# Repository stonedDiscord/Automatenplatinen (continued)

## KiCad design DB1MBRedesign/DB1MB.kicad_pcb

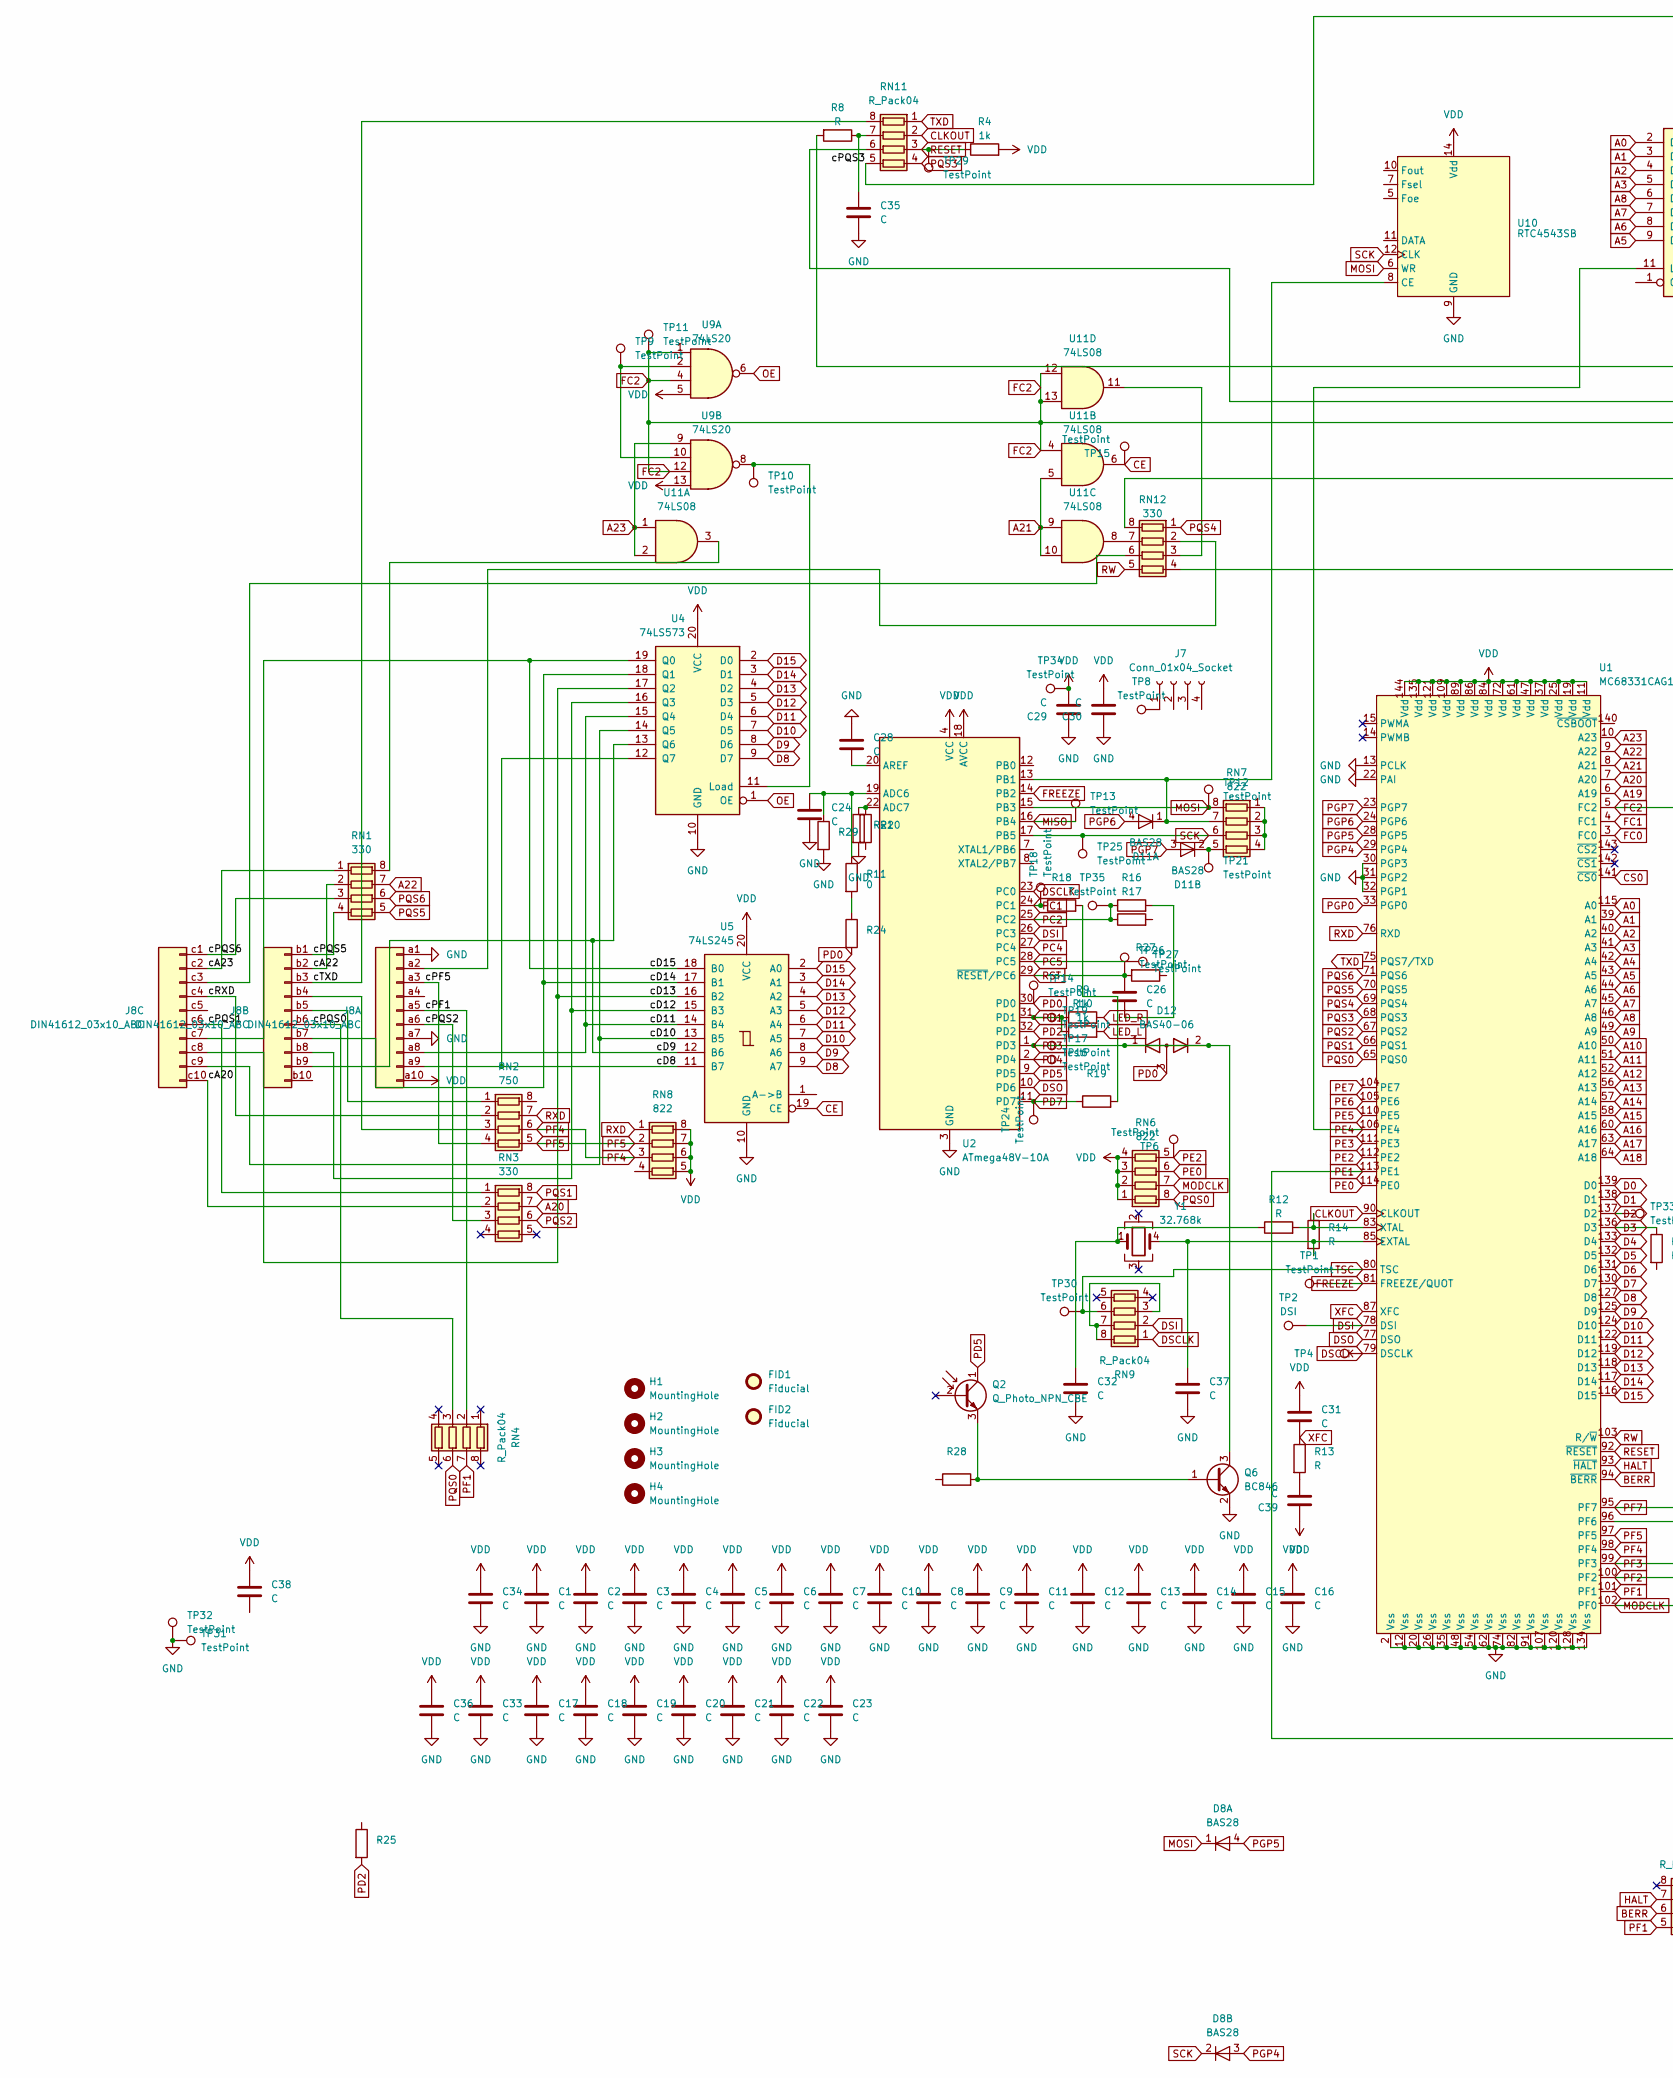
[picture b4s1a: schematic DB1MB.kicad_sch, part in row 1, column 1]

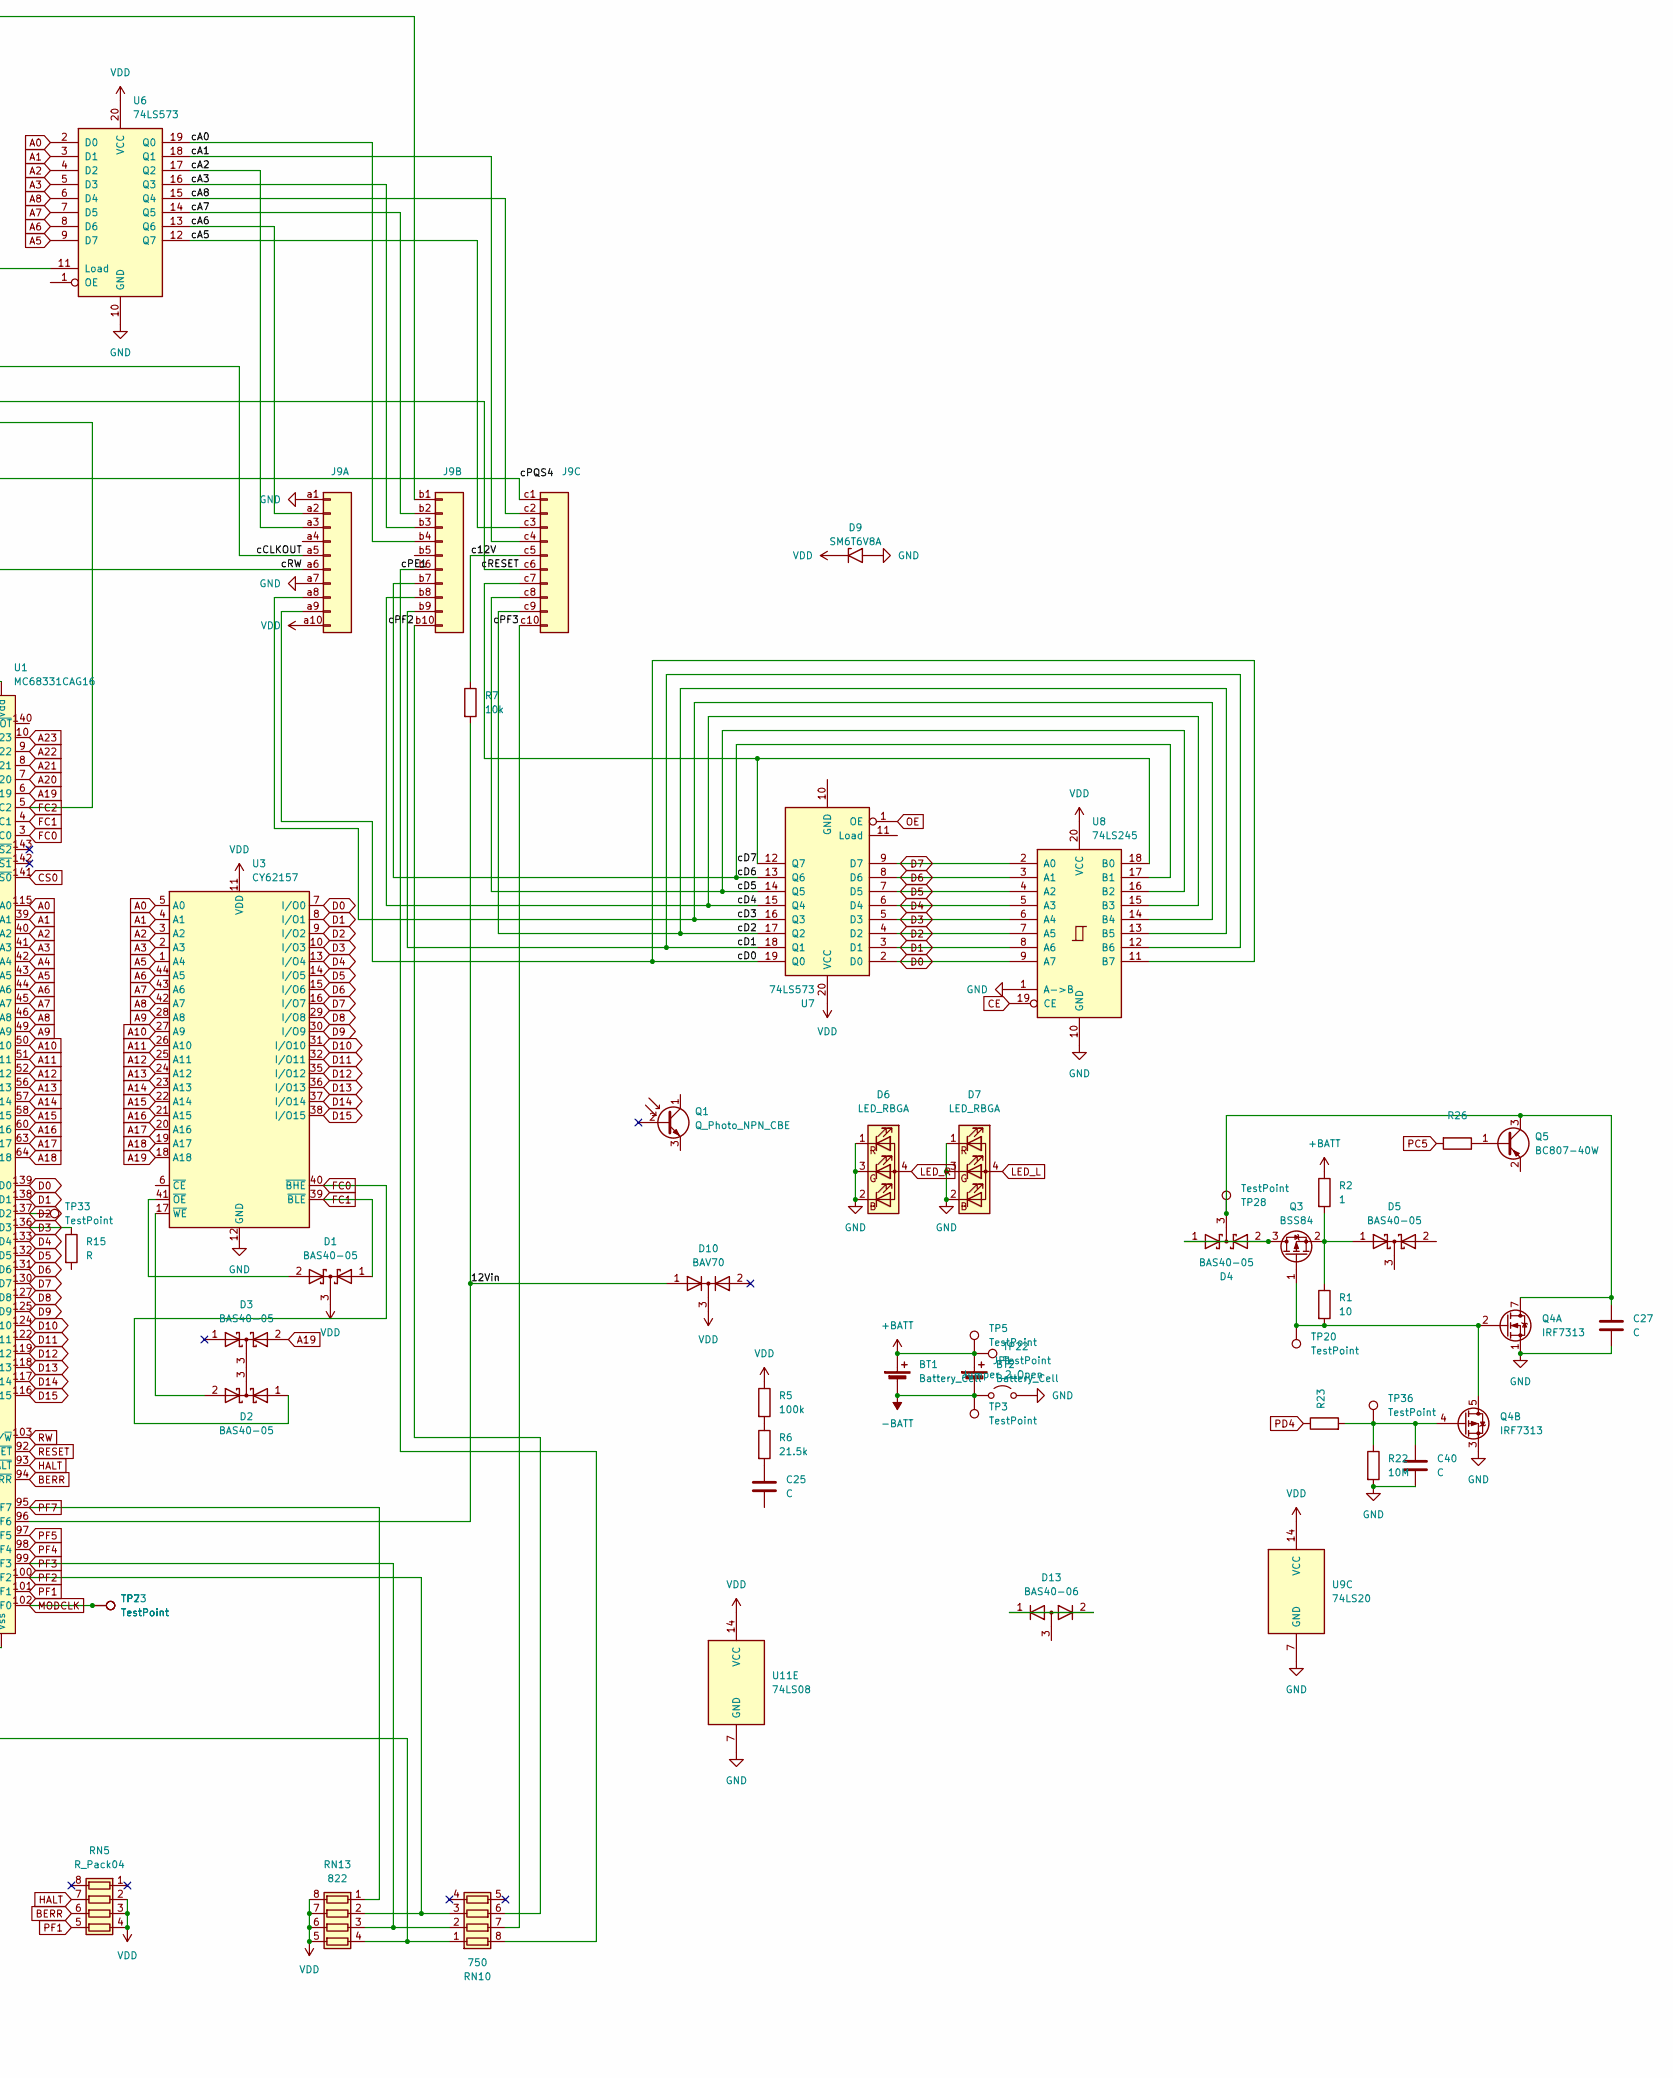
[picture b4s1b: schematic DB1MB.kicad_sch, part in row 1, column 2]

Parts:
BT1, BT2: Battery_Cell; Battery_CR2450
C1, C2, C3, C4, C5, C6, C7, C8, C9, C10, C11, C12, C13, C14, C15, C16, C17, C18, C19, C20, C21, C22, C23, C25, C26, C27, C28, C29, C30, C31, C32, C33, C34, C35, C36, C37, C39: C; C_0805_2012Metric
C24, C38, C40: C; C_1206_3216Metric
D1, D2, D3, D4, D5: BAS40-05; SOT-23-3
D6, D7: LED_RBGA; LED_Cree-PLCC4_3.2x2.8mm_CCW
D8, D11: BAS28; SOT-143
D9: SM6T6V8A; D_SMB
D10: BAV70; TSOT-23
D12, D13: BAS40-06; TSOT-23
FID1, FID2: Fiducial; Fiducial_0.75mm_Mask2.25mm
H1, H2, H3, H4: MountingHole; MountingHole_2.1mm
J7: Conn_01x04_Socket; Deckel
J8, J9: DIN41612_03x10_ABC; DIN41612_R3_3x10_Male_Vertical_THT
JP1: Jumper_2_Open; SolderJumper-2_P1.3mm_Open_Pad1.0x1.5mm
Q1, Q2: Q_Photo_NPN_CBE; Osram_SMD-SmartDIL
Q3: BSS84; SOT-23-3
Q4: IRF7313; SOIC-8_3.9x4.9mm_P1.27mm
Q5: BC807-40W; TSOT-23
Q6: BC846; SOT-23
R1: 10; R_0805_2012Metric
R2: 1; R_0805_2012Metric
R4, R9, R10: 1k; R_0603_1608Metric
R5: 100k; R_0603_1608Metric
R6: 21.5k; R_0603_1608Metric
R7: 10k; R_0603_1608Metric
R8, R12, R13, R15: R; R_0603_1608Metric
R11: 0; R_0603_1608Metric
R14: R; R_1206_3216Metric
R16, R17, R18, R19, R20, R21, R23, R24, R25, R26, R27, R28, R29: R_0603_1608Metric
R22: 10M; R_1206_3216Metric
RN1, RN3, RN12: 330; R_Array_Concave_4x0603
RN2, RN10: 750; R_Array_Concave_4x0603
RN4, RN5, RN9, RN11: R_Pack04; R_Array_Concave_4x0603
RN6, RN7, RN8, RN13: 822; R_Array_Concave_4x0603
TP1, TP6, TP7, TP8, TP9, TP10, TP11, TP12, TP13, TP14, TP15, TP16, TP17, TP18, TP19, TP20, TP21, TP24, TP25, TP26, TP27, TP28, TP29, TP30, TP34, TP35: TestPoint; TestPoint_Pad_D1.0mm
TP2: DSI; TestPoint_Pad_D1.0mm
TP3, TP5, TP32, TP36: TestPoint; TestPoint_Pad_D1.5mm
TP4: DSCLK; TestPoint_Pad_D1.0mm
TP22, TP23, TP31, TP33: TestPoint; TestPoint_Pad_1.0x1.0mm
U1: MC68331CAG16; TQFP-144_20x20mm_P0.5mm
U2: ATmega48V-10A; TQFP-32_7x7mm_P0.8mm
U3: CY62157; TSOP-II-44_10.16x18.41mm_P0.8mm
U4, U6, U7: 74LS573; TSSOP-20_4.4x6.5mm_P0.65mm
U5, U8: 74LS245; TSSOP-20_4.4x6.5mm_P0.65mm
U9: 74LS20; TSSOP-14_4.4x5mm_P0.65mm
U10: RTC4543SB; SOP-18_5.4x11.4mm_P1.27mm
U11: 74LS08; TSSOP-14_4.4x5mm_P0.65mm
Y1: 32.768k; Crystal_SMD_SeikoEpson_MC306-4Pin_8.0x3.2mm

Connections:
+BATT: BT1.1 (+), BT2.1 (+), R2.1, TP5.1 (1_1), TP22.1 (1_1)
-BATT: BT1.2 (-), BT2.2 (-), JP1.1 (A), TP3.1 (1_1)
/12Vin: D10.1 (A), R7.2, U1.96 (PF6)
/c12V: J9.c5, R7.1
/cA0: J9.b4, U6.19 (Q0)
/cA1: J9.c4, U6.18 (Q1)
/cA2: J9.a3, U6.17 (Q2)
/cA3: J9.b3, U6.16 (Q3)
/cA5: J9.c3, U6.12 (Q7)
/cA6: J9.a2, U6.13 (Q6)
/cA7: J9.b2, U6.14 (Q5)
/cA8: J9.c2, U6.15 (Q4)
/cA20: J8.c10, RN3.2 (R2.1)
/cA22: J8.b2, RN1.2 (R2.1)
/cA23: J8.c2, RN1.1 (R1.1)
/cCLKOUT: J9.a5, R8.2
/cD0: J9.a9, U7.19 (Q0), U8.11 (B7)
/cD1: J9.b9, U7.18 (Q1), U8.12 (B6)
/cD2: J9.c9, U7.17 (Q2), U8.13 (B5)
/cD3: J9.a8, U7.16 (Q3), U8.14 (B4)
/cD4: J9.b8, U7.15 (Q4), U8.15 (B3)
/cD5: J9.c8, U7.14 (Q5), U8.16 (B2)
/cD6: J9.b7, U7.13 (Q6), U8.17 (B1)
/cD7: J9.c7, U7.12 (Q7), U8.18 (B0)
/cD8: J8.a9, U4.12 (Q7), U5.11 (B7)
/cD9: J8.b9, U4.13 (Q6), U5.12 (B6)
/cD10: J8.c9, U4.14 (Q5), U5.13 (B5)
/cD11: J8.a8, U4.15 (Q4), U5.14 (B4)
/cD12: J8.b8, U4.16 (Q3), U5.15 (B3)
/cD13: J8.c8, U4.17 (Q2), U5.16 (B2)
/cD14: J8.b7, U4.18 (Q1), U5.17 (B1)
/cD15: J8.c7, U4.19 (Q0), U5.18 (B0)
/cPE1: J9.b6, RN10.8 (R1.2)
/cPF1: J8.a5, RN4.2 (R2.1)
/cPF2: J9.b10, RN10.6 (R3.2)
/cPF3: J9.c10, RN10.7 (R2.2)
/cPF5: J8.a3, RN2.4 (R4.1)
/cPQS0: J8.b6, RN4.3 (R3.1)
/cPQS1: J8.c6, RN3.1 (R1.1)
/cPQS2: J8.a6, RN3.3 (R3.1)
/cPQS3: J9.b1, RN11.5 (R4.2)
/cPQS4: J9.c1, RN12.8 (R1.2)
/cPQS5: J8.b1, RN1.4 (R4.1)
/cPQS6: J8.c1, RN1.3 (R3.1)
/cRESET: J9.c6, RN11.6 (R3.2)
/cRW: J9.a6, RN12.4 (R4.1)
/cRXD: J8.c4, RN2.2 (R2.1)
/cTXD: J8.b3, RN11.8 (R1.2)
A0: U1.115 (A0), U3.5 (A0), U6.2 (D0)
A1: U1.39 (A1), U3.4 (A1), U6.3 (D1)
A2: U1.40 (A2), U3.3 (A2), U6.4 (D2)
A3: U1.41 (A3), U3.2 (A3), U6.5 (D3)
A4: U1.42 (A4)
A5: U1.43 (A5), U3.1 (A4), U6.9 (D7)
A6: U1.44 (A6), U3.44 (A5), U6.8 (D6)
A7: U1.45 (A7), U3.43 (A6), U6.7 (D5)
A8: U1.46 (A8), U3.42 (A7), U6.6 (D4)
A9: U1.49 (A9), U3.28 (A8)
A10: U1.50 (A10), U3.27 (A9)
A11: U1.51 (A11), U3.26 (A10)
A12: U1.52 (A12), U3.25 (A11)
A13: U1.56 (A13), U3.24 (A12)
A14: U1.57 (A14), U3.23 (A13)
A15: U1.58 (A15), U3.22 (A14)
A16: U1.60 (A16), U3.21 (A15)
A17: U1.63 (A17), U3.20 (A16)
A18: U1.64 (A18), U3.19 (A17)
A19: D3.2 (A), U1.6 (A19), U3.18 (A18)
A20: RN3.7 (R2.2), U1.7 (A20)
A21: U1.8 (A21), U11.5, U11.9, U11.10
A22: RN1.7 (R2.2), U1.9 (A22)
A23: U1.10 (A23), U9.9, U11.1, U11.2
BERR: RN5.6 (R3.2), U1.94 (~BERR)
CE: TP15.1 (1_1), U5.19 (CE), U8.19 (CE), U11.6
CLKOUT: RN11.2 (R2.1), U1.90 (CLKOUT)
CS0: U1.141 (~CS0)
D0: U1.139 (D0), U3.7 (I/O0), U7.2 (D0), U8.9 (A7)
D1: U1.138 (D1), U3.8 (I/O1), U7.3 (D1), U8.8 (A6)
D2: TP33.1 (1_1), U1.137 (D2), U3.9 (I/O2), U7.4 (D2), U8.7 (A5)
D3: R15.1, U1.136 (D3), U3.10 (I/O3), U7.5 (D3), U8.6 (A4)
D4: U1.133 (D4), U3.13 (I/O4), U7.6 (D4), U8.5 (A3)
D5: U1.132 (D5), U3.14 (I/O5), U7.7 (D5), U8.4 (A2)
D6: U1.131 (D6), U3.15 (I/O6), U7.8 (D6), U8.3 (A1)
D7: U1.130 (D7), U3.16 (I/O7), U7.9 (D7), U8.2 (A0)
D8: U1.127 (D8), U3.29 (I/O8), U4.9 (D7), U5.9 (A7)
D9: U1.125 (D9), U3.30 (I/O9), U4.8 (D6), U5.8 (A6)
D10: U1.124 (D10), U3.31 (I/O10), U4.7 (D5), U5.7 (A5)
D11: U1.122 (D11), U3.32 (I/O11), U4.6 (D4), U5.6 (A4)
D12: U1.119 (D12), U3.35 (I/O12), U4.5 (D3), U5.5 (A3)
D13: U1.118 (D13), U3.36 (I/O13), U4.4 (D2), U5.4 (A2)
D14: U1.117 (D14), U3.37 (I/O14), U4.3 (D1), U5.3 (A1)
D15: U1.116 (D15), U3.38 (I/O15), U4.2 (D0), U5.2 (A0)
DSCLK: RN9.1 (R1.1), TP4.1 (1_1), U1.79 (DSCLK), U2.23 (PC0)
DSI: RN9.2 (R2.1), TP2.1 (1_1), U1.78 (DSI), U2.26 (PC3)
DSO: U1.77 (DSO), U2.10 (PD6)
FC0: D2.1 (A), U1.3 (FC0), U3.40 (~BHE)
FC1: D1.1 (A), U1.4 (FC1), U3.39 (~BLE)
FC2: TP11.1 (1_1), U1.5 (FC2), U9.1, U9.4, U9.12, U11.4, U11.12, U11.13
FREEZE: TP1.1 (1_1), U1.81 (FREEZE/QUOT), U2.14 (PB2)
GND: C1.2, C2.2, C3.2, C4.2, C5.2, C6.2, C7.2, C8.2, C9.2, C10.2, C11.2, C12.2, C13.2, C14.2, C15.2, C16.2, C17.2, C18.2, C19.2, C20.2, C21.2, C22.2, C23.2, C24.2, C27.2, C28.1, C29.1, C30.1, C32.2, C33.2, C34.2, C35.2, C36.2, C37.2, C40.2, D6.1 (RK), D6.2 (BK), D6.3 (GK), D7.1 (RK), D7.2 (BK), D7.3 (GK), D9.2 (A2), J8.a1, J8.a7, J9.a1, J9.a7, JP1.2 (B), Q4.1 (S), Q4.3 (1), Q6.2 (E), R21.2, R22.2, R29.2, TP31.1 (1_1), TP32.1 (1_1), U1.2 (Vss), U1.12 (Vss), U1.13 (PCLK), U1.20 (Vss), U1.22 (PAI), U1.26 (Vss), U1.30 (PGP3), U1.31 (PGP2), U1.32 (PGP1), U1.35 (Vss), U1.48 (Vss), U1.54 (Vss), U1.62 (Vss), U1.74 (Vss), U1.82 (Vss), U1.91 (Vss), U1.107 (Vss), U1.120 (Vss), U1.128 (Vss), U1.134 (Vss), U2.3 (GND), U2.5 (GND), U2.21 (GND), U3.12 (GND), U3.34 (GND), U4.10 (GND), U5.10 (GND), U6.10 (GND), U8.1 (A->B), U8.10 (GND), U9.7 (GND), U10.9 (GND), U11.7 (GND)
HALT: RN5.7 (R2.2), U1.93 (~HALT)
LED_L: D7.4 (A), R10.2
LED_R: D6.4 (A), R9.2
MISO: TP13.1 (1_1), U2.16 (PB4)
MODCLK: RN6.7 (R2.2), TP7.1 (1_1), TP23.1 (1_1), U1.102 (PF0)
MOSI: D8.1 (K), RN7.8 (R1.2), TP12.1 (1_1), U2.15 (PB3), U10.6 (WR)
unnamed: C25.1, R6.2
unnamed: C26.2, R16.2
unnamed: C32.1, R12.1, Y1.1
unnamed: C39.2, R13.2
unnamed: D2.3 (K), D3.3 (K)
unnamed: C27.1, D4.3 (K), Q4.7 (D), Q4.8 (D), Q5.3 (C), TP28.1 (1_1)
unnamed: D11.1 (K), RN7.7 (R2.2), U2.13 (PB1), U10.8 (CE)
unnamed: D11.2 (K), RN7.5 (R4.2), TP21.1 (1_1)
unnamed: D13.1 (K), D13.2 (K)
unnamed: J7.1 (Pin_1_1), TP8.1 (1_1)
unnamed: J8.a2, RN12.2 (R2.1)
unnamed: J8.b4, RN2.3 (R3.1)
unnamed: J8.b5, RN2.1 (R1.1)
unnamed: J8.c3, RN12.6 (R3.2)
unnamed: Q2.3 (E), Q6.1 (B), R28.2
unnamed: D4.1 (A), D4.2 (A), Q3.3 (D)
unnamed: Q3.1 (G), Q4.2 (G), Q4.5 (D), Q4.6 (D), R1.2, TP20.1 (1_1)
unnamed: D5.1 (A_1), Q3.2 (S), R1.1, R2.2
unnamed: C40.1, Q4.4 (G), R22.1, R23.2, TP36.1 (1_1)
unnamed: Q5.1 (B), R26.1
unnamed: R5.2, R6.1
unnamed: R11.2, R24.1
unnamed: R18.2, R19.2
unnamed: RN1.8 (R1.2), U11.3
unnamed: RN7.1 (R1.1), RN7.2 (R2.1), RN7.3 (R3.1), RN7.4 (R4.1)
unnamed: RN9.3 (R3.1), RN9.7 (R2.2), RN9.8 (R1.2)
unnamed: C35.1, R8.1, RN11.7 (R2.2)
unnamed: RN12.7 (R2.2), U11.8
unnamed: RN12.3 (R3.1), U11.11
unnamed: TP9.1 (1_1), U9.2, U9.10
unnamed: C37.1, R14.2, U1.85 (EXTAL), Y1.4
unnamed: R12.2, R14.1, U1.83 (XTAL)
unnamed: C24.1, R11.1, R29.1, U2.19 (ADC6)
unnamed: R20.1, R21.1, U2.22 (ADC7)
unnamed: C28.2, U2.20 (AREF)
unnamed: D1.2 (A), U3.41 (~OE)
unnamed: D2.2 (A), U3.17 (~WE)
unnamed: TP10.1 (1_1), U4.11 (Load), U9.8
OE: U4.1 (OE), U7.1 (OE), U9.6
PC1: R18.1, TP18.1 (1_1), U2.24 (PC1)
PC2: R16.1, R17.1, TP35.1 (1_1), U2.25 (PC2)
PC4: U2.27 (PC4)
PC5: R26.2, TP27.1 (1_1), U2.28 (PC5)
PD0: D12.3 (A), R24.2, TP14.1 (1_1), U2.30 (PD0)
PD1: R9.1, R10.1, TP19.1 (1_1), U2.31 (PD1)
PD2: R25.2, U2.32 (PD2)
PD3: D12.1 (K), D12.2 (K), Q6.3 (C), TP17.1 (1_1), U2.1 (PD3)
PD4: R23.1, TP16.1 (1_1), U2.2 (PD4)
PD5: Q2.1 (C), U2.9 (PD5)
PD7: R19.1, TP24.1 (1_1), U2.11 (PD7)
PE0: RN6.6 (R3.2), U1.114 (PE0)
PE1: RN10.1 (R1.1), RN13.4 (R4.1), U1.113 (PE1)
PE2: RN6.5 (R4.2), TP6.1 (1_1), U1.112 (PE2)
PE3: U1.111 (PE3)
PE4: U1.106 (PE4), U6.11 (Load)
PE5: U1.110 (PE5)
PE6: U1.105 (PE6)
PE7: U1.104 (PE7)
PF1: RN4.7 (R2.2), RN5.5 (R4.2), U1.101 (PF1)
PF2: RN10.3 (R3.1), RN13.2 (R2.1), U1.100 (PF2)
PF3: RN10.2 (R2.1), RN13.3 (R3.1), U1.99 (PF3)
PF4: RN2.6 (R3.2), RN8.3 (R3.1), U1.98 (PF4)
PF5: RN2.5 (R4.2), RN8.2 (R2.1), U1.97 (PF5)
PF7: RN13.1 (R1.1), U1.95 (PF7)
PGP0: U1.33 (PGP0)
PGP4: D8.3 (A), U1.29 (PGP4)
PGP5: D8.4 (A), U1.28 (PGP5)
PGP6: D11.4 (A), U1.24 (PGP6)
PGP7: D11.3 (A), U1.23 (PGP7)
PQS0: RN4.6 (R3.2), RN6.8 (R1.2), U1.65 (PQS0)
PQS1: RN3.8 (R1.2), U1.66 (PQS1)
PQS2: RN3.6 (R3.2), U1.67 (PQS2)
PQS3: RN11.4 (R4.1), U1.68 (PQS3)
PQS4: RN12.1 (R1.1), U1.69 (PQS4)
PQS5: RN1.5 (R4.2), U1.70 (PQS5)
PQS6: RN1.6 (R3.2), U1.71 (PQS6)
RESET: R4.1, RN11.3 (R3.1), TP29.1 (1_1), U1.92 (~RESET)
RST: C26.1, R27.2, TP26.1 (1_1), U2.29 (~RESET/PC6)
RW: RN12.5 (R4.2), U1.103 (R/~W)
RXD: RN2.7 (R2.2), RN8.1 (R1.1), U1.76 (RXD)
SCK: D8.2 (K), RN7.6 (R3.2), TP25.1 (1_1), U2.17 (PB5), U10.12 (CLK)
TSC: RN9.6 (R3.2), TP30.1 (1_1), U1.80 (TSC)
TXD: RN11.1 (R1.1), U1.75 (PQS7/TXD)
VDD: C1.1, C2.1, C3.1, C4.1, C5.1, C6.1, C7.1, C8.1, C9.1, C10.1, C11.1, C12.1, C13.1, C14.1, C15.1, C16.1, C17.1, C18.1, C19.1, C20.1, C21.1, C22.1, C23.1, C29.2, C30.2, C31.1, C33.1, C34.1, C36.1, C38.1, C39.1, D1.3 (K), D9.1 (A1), D10.3 (K), J8.a10, J9.a10, R4.2, R5.1, RN5.2 (R2.1), RN5.3 (R3.1), RN5.4 (R4.1), RN6.1 (R1.1), RN6.2 (R2.1), RN6.3 (R3.1), RN6.4 (R4.1), RN8.5 (R4.2), RN8.6 (R3.2), RN8.7 (R2.2), RN8.8 (R1.2), RN13.5 (R4.2), RN13.6 (R3.2), RN13.7 (R2.2), RN13.8 (R1.2), TP34.1 (1_1), U1.11 (Vdd), U1.19 (Vdd), U1.25 (Vdd), U1.37 (Vdd), U1.47 (Vdd), U1.61 (Vdd), U1.72 (Vdd), U1.84 (Vdd), U1.86 (Vdd), U1.89 (Vdd), U1.109 (Vdd), U1.121 (Vdd), U1.135 (Vdd), U1.144 (Vdd), U2.4 (VCC), U2.6 (VCC), U2.18 (AVCC), U3.11 (VDD), U3.33 (VDD), U4.20 (VCC), U5.20 (VCC), U6.20 (VCC), U7.20 (VCC), U8.20 (VCC), U9.5, U9.13, U9.14 (VCC), U10.14 (Vdd), U11.14 (VCC)
XFC: C31.2, R13.1, U1.87 (XFC)

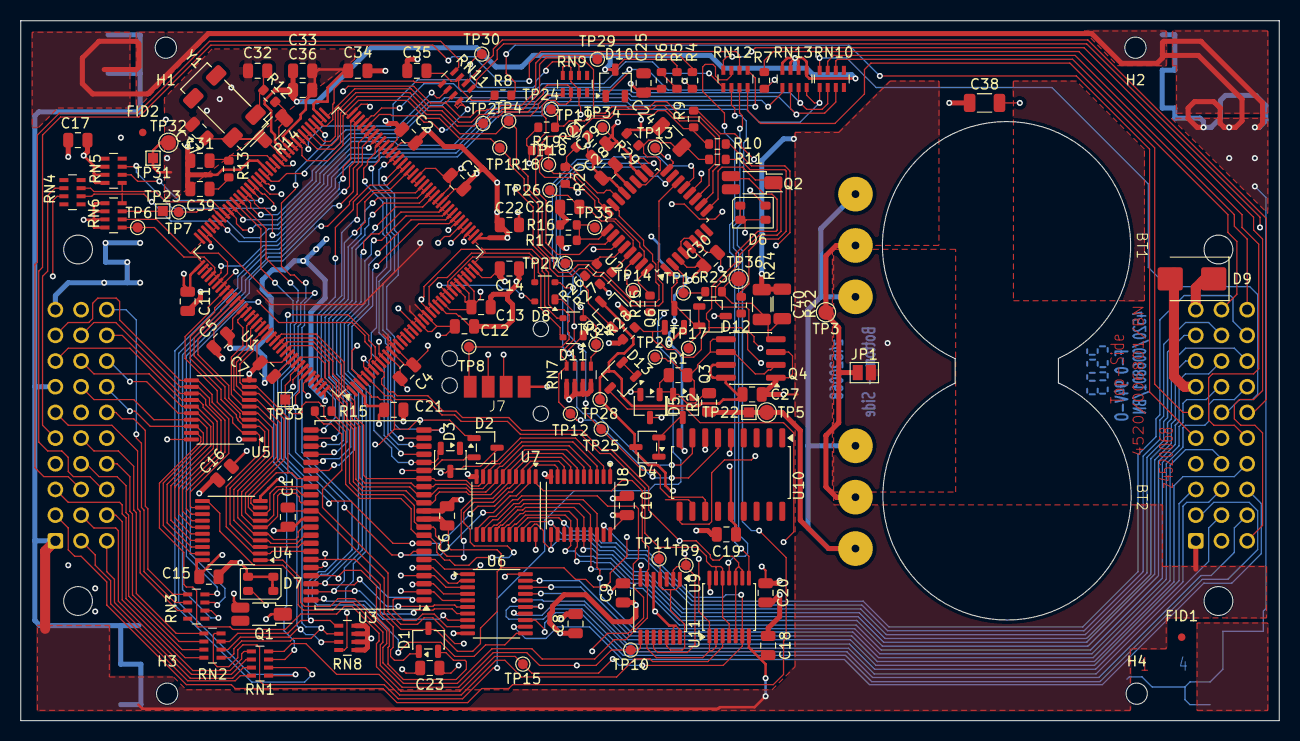
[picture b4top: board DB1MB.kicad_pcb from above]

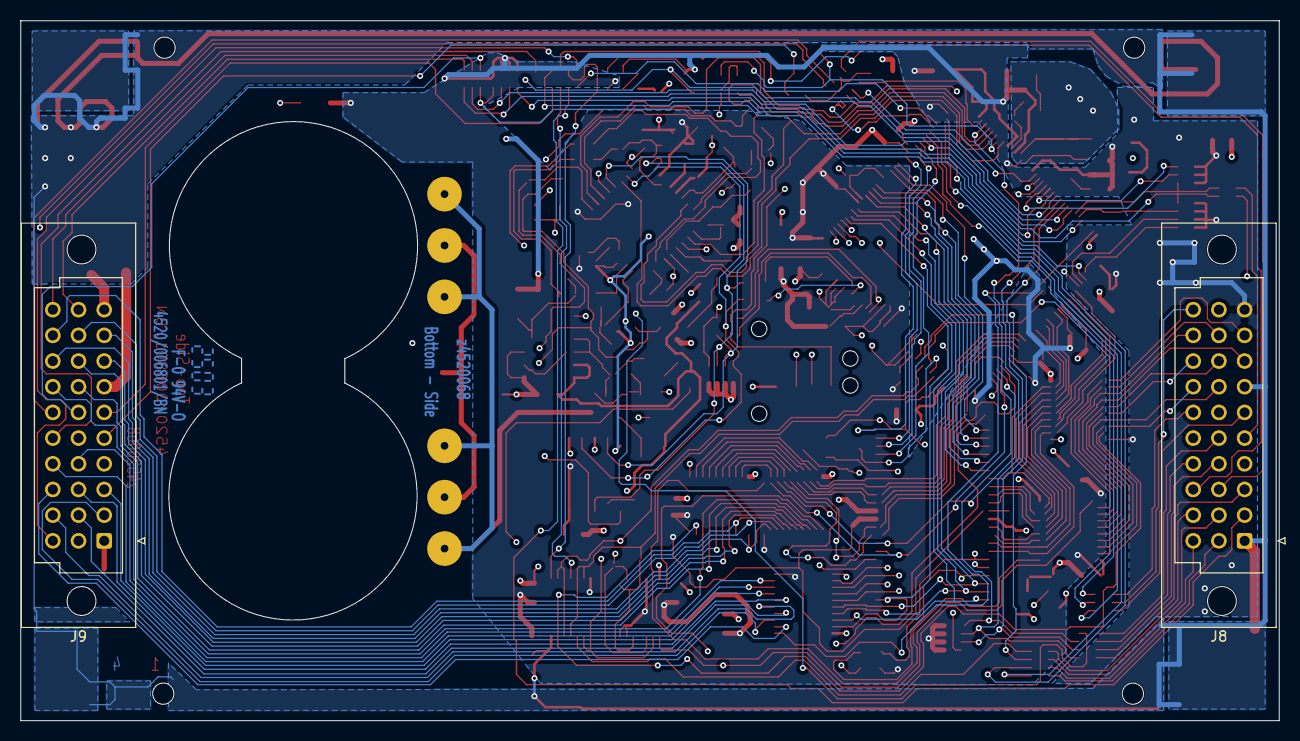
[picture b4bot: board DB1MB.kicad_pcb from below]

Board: 4 copper layers, 124.5 x 69.2 mm, 160 parts (2 on the bottom side), 183 nets.

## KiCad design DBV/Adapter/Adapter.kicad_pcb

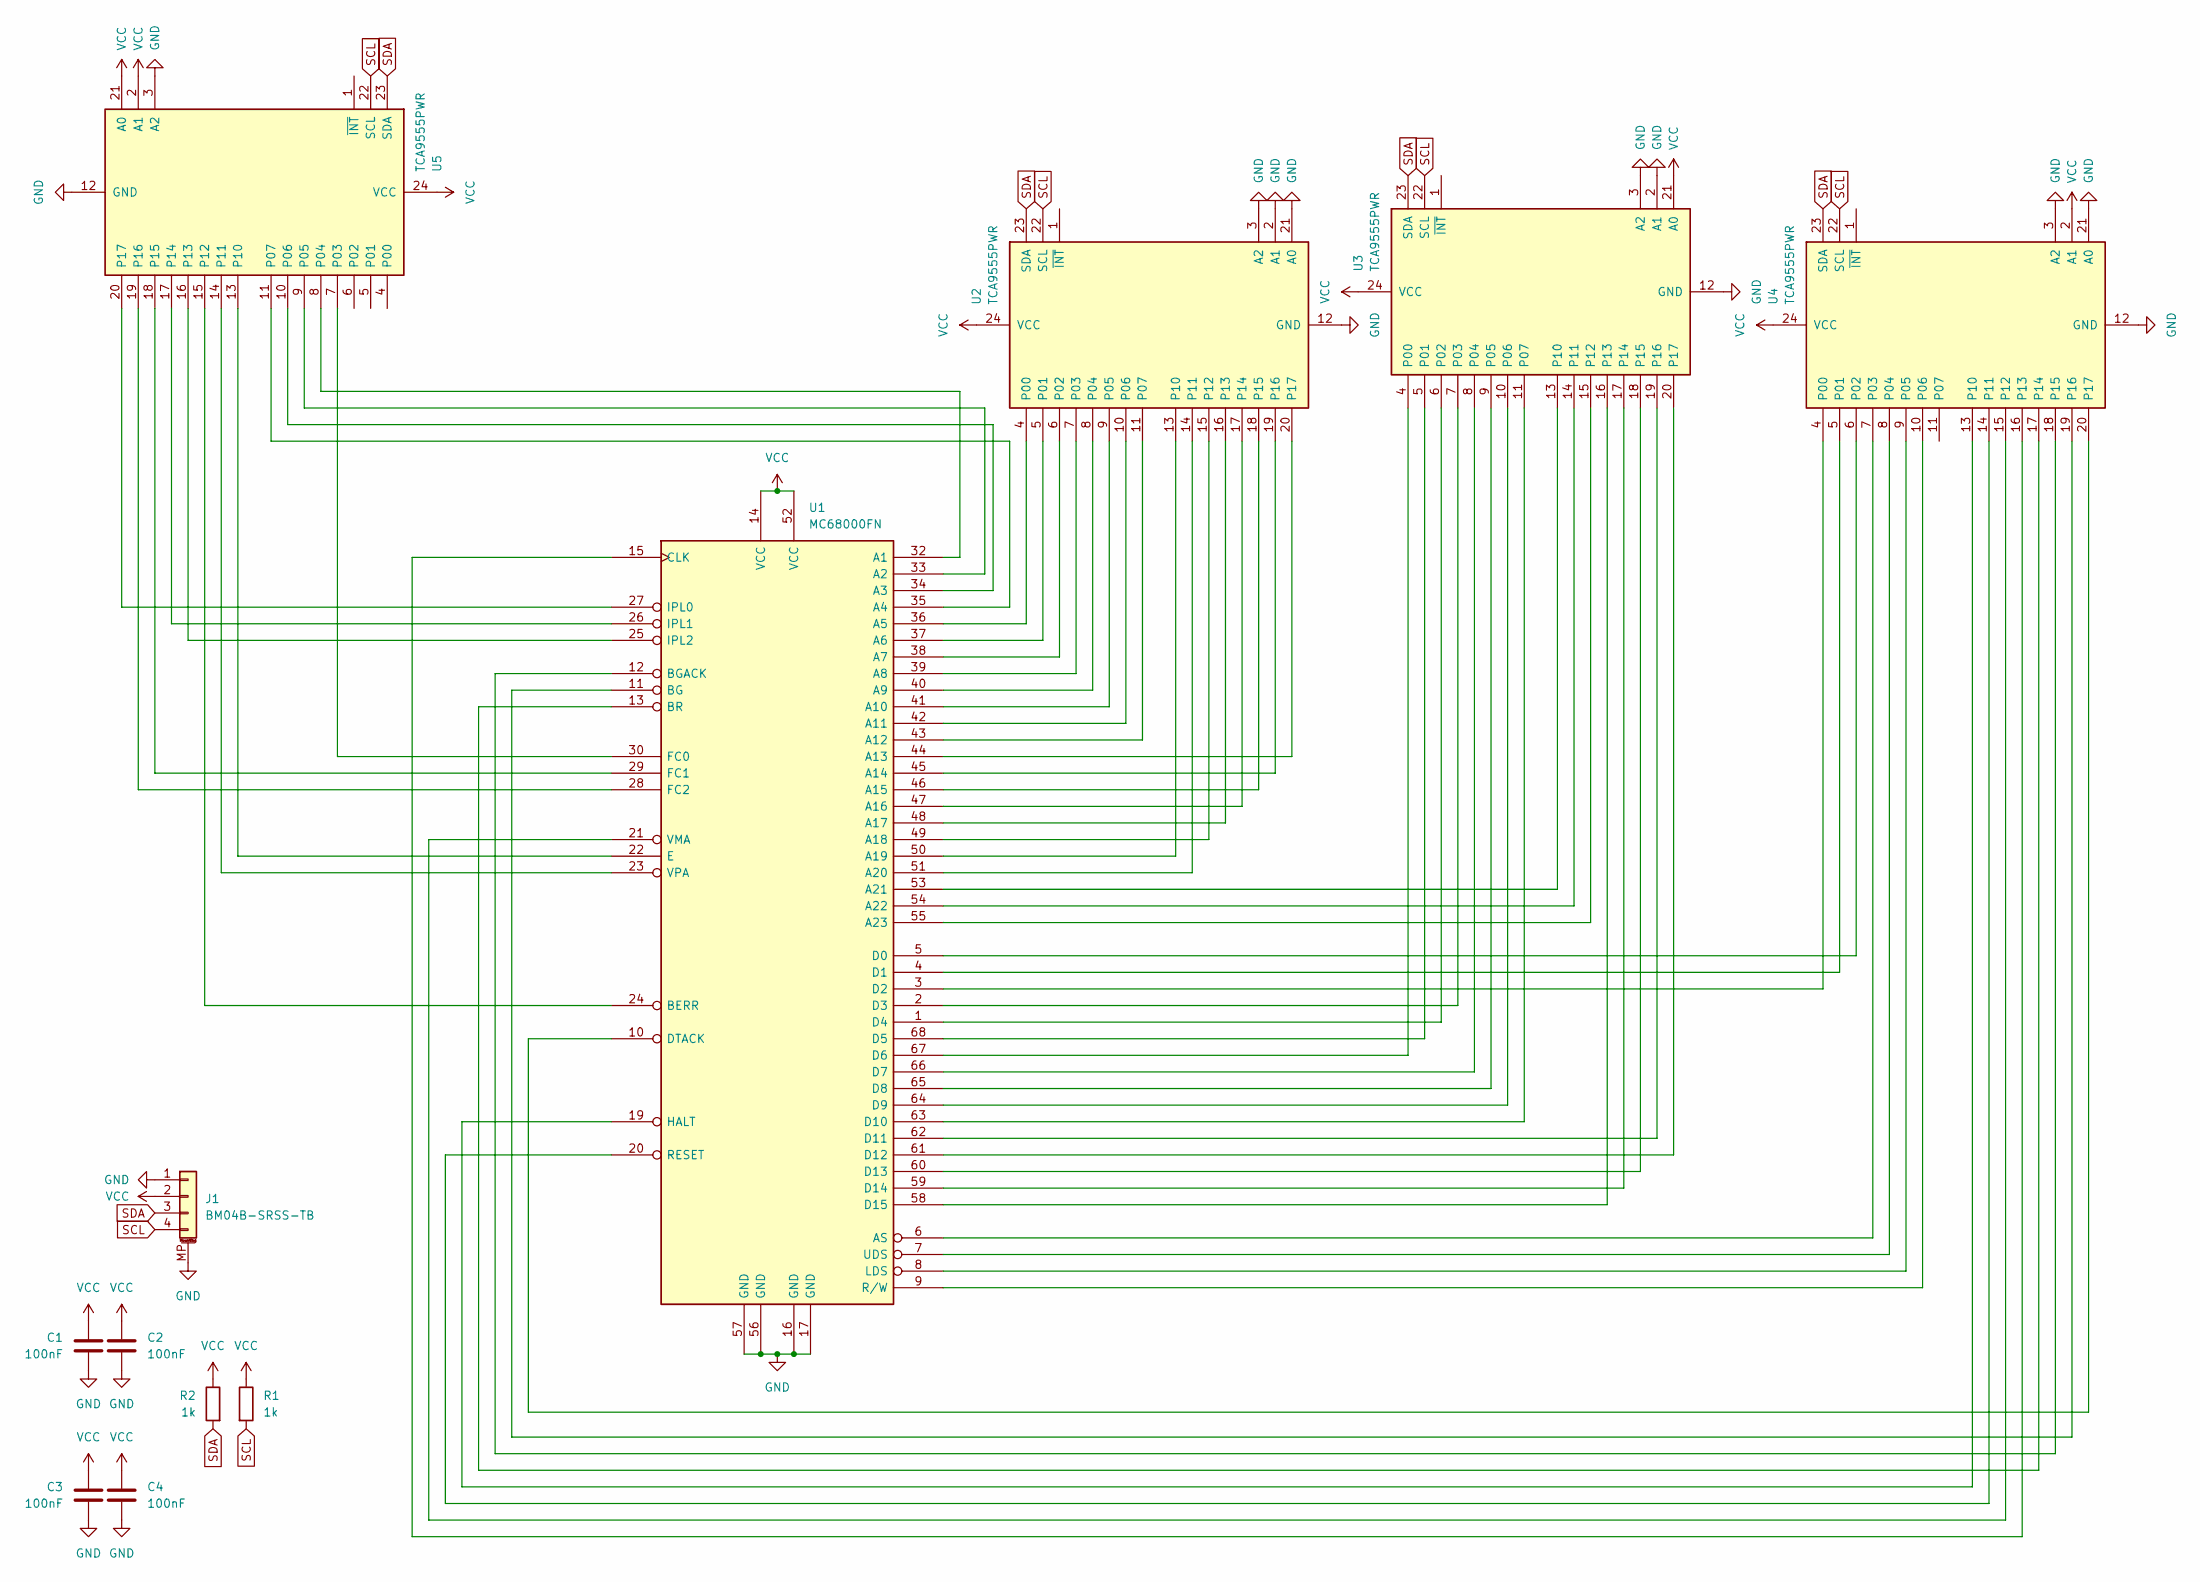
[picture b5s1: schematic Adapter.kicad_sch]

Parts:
C1, C2, C3, C4: 100nF; C_0603_1608Metric
J1: BM04B-SRSS-TB; JST_SH_BM04B-SRSS-TB_1x04-1MP_P1.00mm_Vertical
R1, R2: 1k; R_0603_1608Metric
U1: MC68000FN; PLCC-68_out
U2, U3, U4, U5: TCA9555PWR; TSSOP-24_4.4x7.8mm_P0.65mm

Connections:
GND: C1.2, C2.2, C3.2, C4.2, J1.1, J1.MP (MountPin), U1.16 (GND), U1.17 (GND), U1.56 (GND), U1.57 (GND), U2.2 (A1), U2.3 (A2), U2.12 (GND), U2.21 (A0), U3.2 (A1), U3.3 (A2), U3.12 (GND), U4.3 (A2), U4.12 (GND), U4.21 (A0), U5.3 (A2), U5.12 (GND)
unnamed: U1.32 (A1), U5.8 (P04)
unnamed: U1.33 (A2), U5.9 (P05)
unnamed: U1.34 (A3), U5.10 (P06)
unnamed: U1.35 (A4), U5.11 (P07)
unnamed: U1.36 (A5), U2.4 (P00)
unnamed: U1.37 (A6), U2.5 (P01)
unnamed: U1.38 (A7), U2.6 (P02)
unnamed: U1.39 (A8), U2.7 (P03)
unnamed: U1.40 (A9), U2.8 (P04)
unnamed: U1.41 (A10), U2.9 (P05)
unnamed: U1.42 (A11), U2.10 (P06)
unnamed: U1.43 (A12), U2.11 (P07)
unnamed: U1.44 (A13), U2.20 (P17)
unnamed: U1.45 (A14), U2.19 (P16)
unnamed: U1.46 (A15), U2.18 (P15)
unnamed: U1.47 (A16), U2.17 (P14)
unnamed: U1.48 (A17), U2.16 (P13)
unnamed: U1.49 (A18), U2.15 (P12)
unnamed: U1.50 (A19), U2.13 (P10)
unnamed: U1.51 (A20), U2.14 (P11)
unnamed: U1.53 (A21), U3.13 (P10)
unnamed: U1.54 (A22), U3.14 (P11)
unnamed: U1.55 (A23), U3.15 (P12)
unnamed: U1.6 (AS), U4.7 (P03)
unnamed: U1.24 (BERR), U5.15 (P12)
unnamed: U1.11 (BG), U4.19 (P16)
unnamed: U1.12 (BGACK), U4.18 (P15)
unnamed: U1.13 (BR), U4.17 (P14)
unnamed: U1.15 (CLK), U4.16 (P13)
unnamed: U1.5 (D0), U4.6 (P02)
unnamed: U1.4 (D1), U4.5 (P01)
unnamed: U1.3 (D2), U4.4 (P00)
unnamed: U1.2 (D3), U3.7 (P03)
unnamed: U1.1 (D4), U3.6 (P02)
unnamed: U1.68 (D5), U3.5 (P01)
unnamed: U1.67 (D6), U3.4 (P00)
unnamed: U1.66 (D7), U3.8 (P04)
unnamed: U1.65 (D8), U3.9 (P05)
unnamed: U1.64 (D9), U3.10 (P06)
unnamed: U1.63 (D10), U3.11 (P07)
unnamed: U1.62 (D11), U3.19 (P16)
unnamed: U1.61 (D12), U3.20 (P17)
unnamed: U1.60 (D13), U3.18 (P15)
unnamed: U1.59 (D14), U3.17 (P14)
unnamed: U1.58 (D15), U3.16 (P13)
unnamed: U1.10 (DTACK), U4.20 (P17)
unnamed: U1.22 (E), U5.13 (P10)
unnamed: U1.30 (FC0), U5.7 (P03)
unnamed: U1.29 (FC1), U5.18 (P15)
unnamed: U1.28 (FC2), U5.19 (P16)
unnamed: U1.19 (HALT), U4.13 (P10)
unnamed: U1.27 (IPL0), U5.20 (P17)
unnamed: U1.26 (IPL1), U5.17 (P14)
unnamed: U1.25 (IPL2), U5.16 (P13)
unnamed: U1.8 (LDS), U4.9 (P05)
unnamed: U1.20 (RESET), U4.14 (P11)
unnamed: U1.9 (R/W), U4.10 (P06)
unnamed: U1.7 (UDS), U4.8 (P04)
unnamed: U1.21 (VMA), U4.15 (P12)
unnamed: U1.23 (VPA), U5.14 (P11)
SCL: J1.4, R1.2, U2.22 (SCL), U3.22 (SCL), U4.22 (SCL), U5.22 (SCL)
SDA: J1.3, R2.2, U2.23 (SDA), U3.23 (SDA), U4.23 (SDA), U5.23 (SDA)
VCC: C1.1, C2.1, C3.1, C4.1, J1.2, R1.1, R2.1, U1.14 (VCC), U1.52 (VCC), U2.24 (VCC), U3.21 (A0), U3.24 (VCC), U4.2 (A1), U4.24 (VCC), U5.2 (A1), U5.21 (A0), U5.24 (VCC)

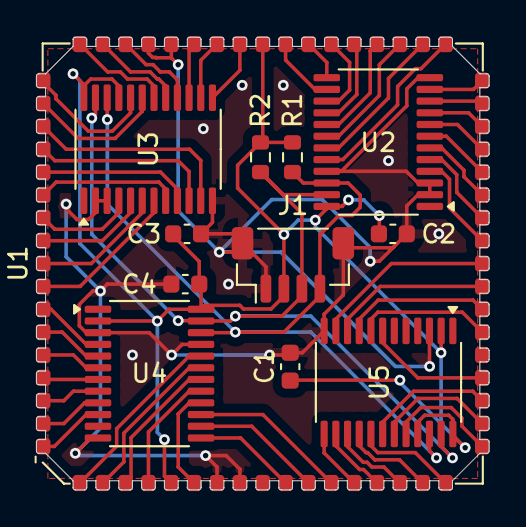
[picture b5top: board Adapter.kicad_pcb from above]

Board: 2 copper layers, 25.1 x 25.1 mm, 12 parts (0 on the bottom side), 64 nets.

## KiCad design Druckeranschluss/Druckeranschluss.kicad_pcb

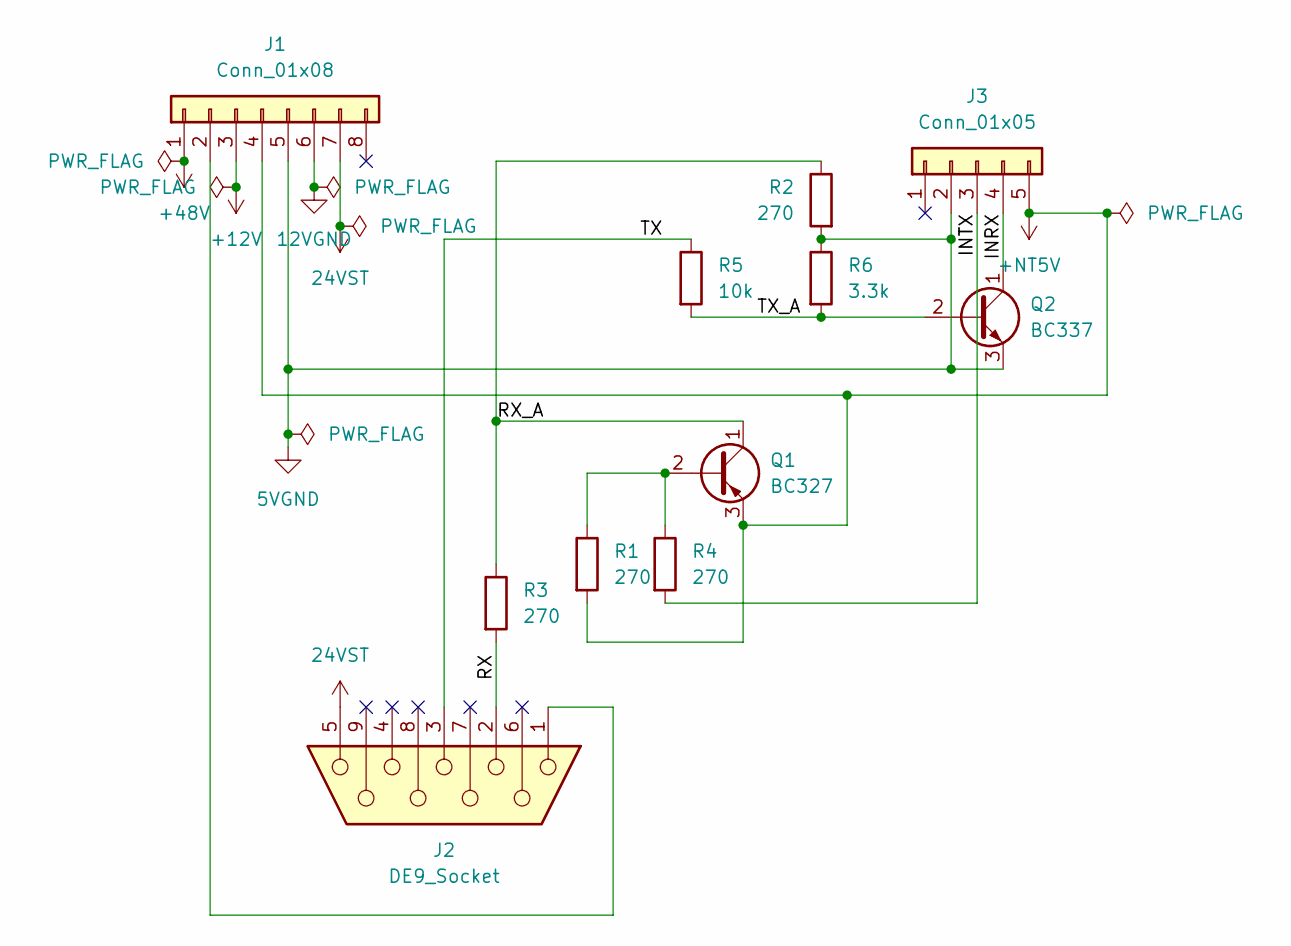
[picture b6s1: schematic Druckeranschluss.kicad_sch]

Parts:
J1: Conn_01x08; PinHeader_1x08_P2.54mm_Horizontal
J2: DE9_Socket; DSUB-9_Socket_Horizontal_P2.77x2.84mm_EdgePinOffset9.40mm
J3: Conn_01x05; PinHeader_1x05_P2.54mm_Horizontal
Q1: BC327; TO-92L_Wide
Q2: BC337; TO-92L_Wide
R1, R2, R3, R4: 270; R_Axial_DIN0207_L6.3mm_D2.5mm_P10.16mm_Horizontal
R5: 10k; R_Axial_DIN0207_L6.3mm_D2.5mm_P10.16mm_Horizontal
R6: 3.3k; R_Axial_DIN0207_L6.3mm_D2.5mm_P10.16mm_Horizontal

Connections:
5VGND: J1.5, J3.2, Q2.3 (E), R2.2, R6.1
12VGND: J1.6
24VST: J1.7, J2.5
+12V: J1.3
+48V: J1.1
+NT5V: J1.4, J3.5, Q1.3 (E), R1.2
/INRX: J3.4, Q2.1 (C)
/INTX: J3.3, R4.2
/RX: J2.2, R3.2
/RX_A: Q1.1 (C), R2.1, R3.1
/TX: J2.3, R5.1
/TX_A: Q2.2 (B), R5.2, R6.2
unnamed: J1.2, J2.1
unnamed: Q1.2 (B), R1.1, R4.1
